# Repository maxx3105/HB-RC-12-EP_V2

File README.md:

# HB-RC-12-EP_V2
12 Tasten Fernbedienung mit E-Paper Display für Homematic

Zusätzlich die Option das E-Paper Display direkt anzuschließen und LiPo Akku per QI Ladefunktion aufzuladen.

Dieses Projekt basiert auf der Arbeit von [pa-pa](https://github.com/pa-pa/AskSinPP) ,[Jérôme](https://github.com/jp112sdl/HB-RC-4-Dis-TH) und [MajorTom](https://github.com/TomMajor/SmartHome/tree/master/PCB/HB-RC-12-EP).

# Hardware

### Bauteile

Bauteile                   | Bezeichnung          | Anzahl | Kommentar        | Quelle   |
-------------------------- | -------------------- | ------ | ---------------- | -------- |
C1,C2,C14,C15,C16,C17      | 100nF, 10%, 50V      |   6    |  X7R-G0805 100N  |Reichelt  |
C18                        | 100µF/10V            |   1    | TAJ 3528 100/10  |Reichelt  |
D1                         | LED rot 12 mcd 160°  |   1    | OSO LHR974       |Reichelt  |
D2                         | LED grün 7.1 mcd 160°|   1    | OSO LGR971       |Reichelt  |
R1, R2                     | 1,5K Ohm             |   2    | RND 0805 1 1,5K  |Reichelt  |
R3                         | 10K Ohm              |   1    | RND 0805 1 10K   |Reichelt  |
U1                         | Atmega 1284P-AU      |   1    | TQFP44           |Reichelt  |
U2                         | CC1101               |   1    | 868Mhz Funkmodul |[eBay](https://www.ebay.de/itm/1-2-5PCS-CC1101-868MHZ-Kabellos-Modul-Long-Distance-Transmission-Antenne-1-8V/322983173720?ssPageName=STRK%3AMEBIDX%3AIT&var=512121286081&_trksid=p2057872.m2749.l2649)|
SW1-13                     | Taster 3x6x2,5mm     |  13    | DTSM-3           |[Aliexpress](https://de.aliexpress.com/item/32672806661.html)|
Q1                         | CSTCE8               |   1    | 8Mhz Resonator   |[Aliexpress](https://de.aliexpress.com/item/32436805954.html?spm=a2g0s.9042311.0.0.27424c4dFOxBvK)|
Q3 Statt Q1                | CSTCC8               |   1    | 8Mhz Resonator   |Reichelt  |

Bauteile ohne Hat          | Bezeichnung          | Anzahl | Kommentar        | Quelle |
-------------------------- | -------------------- | ------ | ---------------- | ------ |
C3-C13                     | 1µF, 10%, 25V        |  11    | KEM X5R0805 1,0U |Reichelt|
D3, D4, D5                 | MBR0530              |   3    | MBR0530T1G ONS   |Reichelt|
C3, ... C13                | 1µF, 10%, 25V        |  11    | KEM X5R0805 1,0U |Reichelt|
R8                         | 100K Ohm             |   1    | RND 0805 1 100K  |Reichelt|
R8-1,R8-2                  | 1,0 Ohm              |   2    | SMD-0805 1,00    |Reichelt|
Q2                         | IRLML 6346           |   1    | IRLML 6346       |Reichelt|
L1                         | Induktivität 68 µH   |   1    | L-1616FPS 68µ    |Reichelt|

Bauteile LiPo              | Bezeichnung          | Anzahl | Kommentar       | Quelle |
-------------------------- | -------------------- | ------ | --------------- | ------ |
C19,C20                    | 10uF, +-20%, 10V     |   2    | KEM X5R0805 10U |Reichelt|
D6                         | LED weiß 520 mcd 120°|   1    | SLO SMD-W0805-0 |Reichelt|
R9                         | 4,7K Ohm             |   1    | RND 0805 1 4,7K |Reichelt|
R10                        | 680 Ohm              |   1    | RND 0805 1 680  |Reichelt|
R11                        | 1K Ohm               |   1    | RND 0805 1 1,0K |Reichelt|
R13                        | 100K Ohm             |   1    | RND 0805 1 100K |Reichelt|
U3                         | MCP 1700T-3002E      |   1    | MCP 1700T-3002E |Reichelt|
U4                         | MCP 73831T-2ACI      |   1    | MCP 73831T-2ACI |Reichelt|
U5                         | PC357                |   1    | PC 357NJ0000F   |Reichelt|

#### Sonstiges

~8,3 cm Draht als Antenne

### Programmieradapter
- 1x ISP (z.B. [diesen hier](https://www.diamex.de/dxshop/USB-ISP-Programmer-fuer-Atmel-AVR-Rev2))

# Software

### Fuses
Ext:  0xFF
High: 0xD2
Low:  0xE2 (0xFF für Externen Takt)

`C:\Program Files (x86)\Arduino\hardware\tools\avr\bin> .\avrdude -C ..\etc\avrdude.conf -p m1284p -P com7 -c stk500 -U lfuse:w:0xE2:m -U hfuse:w:0xD2:m -U efuse:w:0xFF:m`

### Firmware

Projektverzeichnis: [HB-RC-12-EP](https://github.com/jp112sdl/HB-RC-12-EP)

Benötigt werden die Bibliotheken
  - [AskSinPP](https://github.com/pa-pa/AskSinPP) (master-Branch verwenden!)
  - [Low-Power](https://github.com/rocketscream/Low-Power)
  - [EnableInterrupt](https://github.com/GreyGnome/EnableInterrupt)
  - [GxEPD](https://github.com/ZinggJM/GxEPD) 
  - [Adafruit-GFX](https://github.com/adafruit/Adafruit-GFX-Library)
  - [Adafruit-BusIO](https://github.com/adafruit/Adafruit_BusIO)
  - [U8g2_for_Adafruit_GFX](https://github.com/olikraus/U8g2_for_Adafruit_GFX)

# Bauanleitung

https://cdn.thingiverse.com/assets/88/70/7e/3d/6d/Aufbauanleitung_YA_HB-RC-12-EP_Case.pdf

# Bilder

# Links
https://homematic-forum.de/forum/viewtopic.php?f=76&t=50160

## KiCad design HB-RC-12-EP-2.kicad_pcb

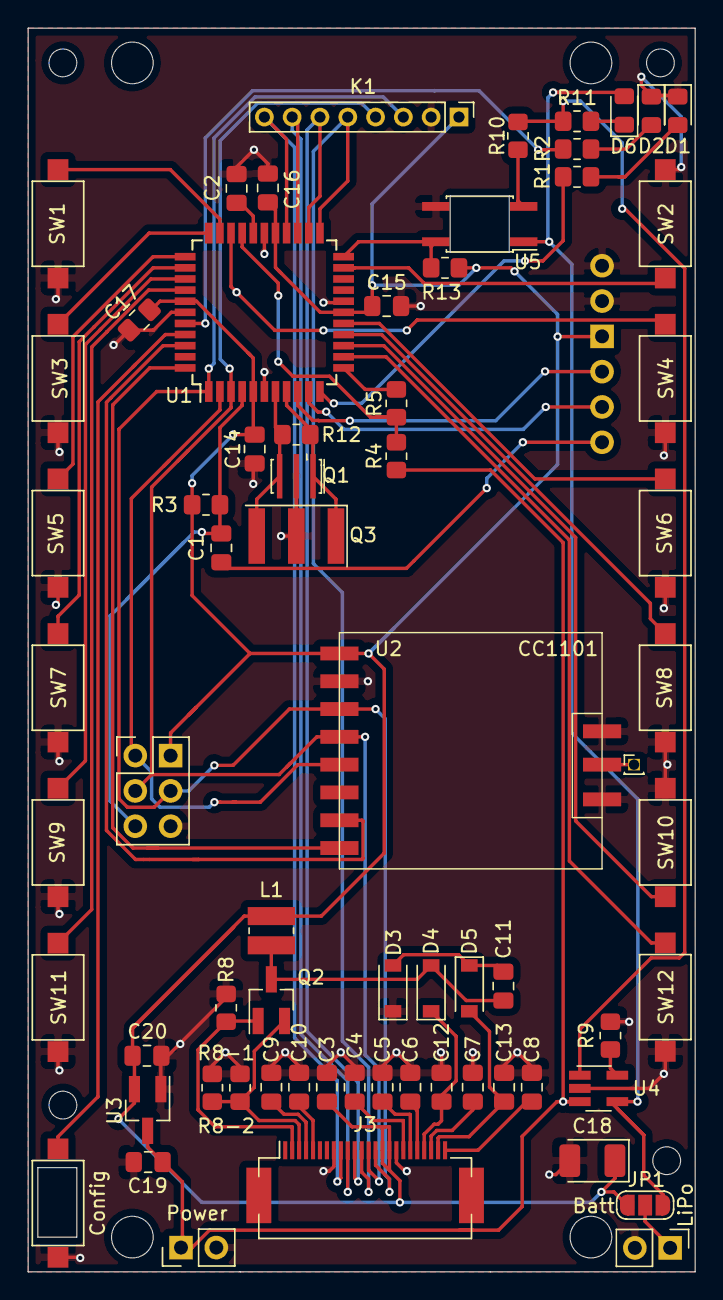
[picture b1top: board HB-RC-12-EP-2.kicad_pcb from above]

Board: 2 copper layers, 48.0 x 89.5 mm, 69 parts (1 on the bottom side), 59 nets.

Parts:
+: Power; PinHeader_1x02_P2.54mm_Vertical
Ant: Ant; PinHeader_1x01_P1.00mm_Vertical
C1, C2, C14, C15, C16, C17: 100n; C_0805_2012Metric_Pad1.18x1.45mm_HandSolder
C3, C4, C5, C6, C7, C8: 1µF/25V; C_0805_2012Metric_Pad1.18x1.45mm_HandSolder
C9, C10, C11, C12, C13: 1µF/50V; C_0805_2012Metric_Pad1.18x1.45mm_HandSolder
C18: 100µ/10V; CP_EIA-3528-21_Kemet-B_Pad1.50x2.35mm_HandSolder
C19, C20: 10/10; C_0805_2012Metric_Pad1.18x1.45mm_HandSolder
Config: SW_Push; SW_SPST_CK_RS282G05A3
D1: LED rt; LED_0805_2012Metric_Pad1.15x1.40mm_HandSolder
D2: gn; LED_0805_2012Metric_Pad1.15x1.40mm_HandSolder
D3, D4, D5: MBR0530; D_SOD-123
D6: LED wt; LED_0805_2012Metric_Pad1.15x1.40mm_HandSolder
FTDI1: FTDI; PinHeader_1x06_P2.54mm_Vertical
ISP1: ISP; PinHeader_2x03_P2.54mm_Vertical
J3: eInk; Hirose_FH12-24S-0.5SH_1x24-1MP_P0.50mm_Horizontal
JP1: SolderJumper_3_Open; SolderJumper-3_P1.3mm_Open_RoundedPad1.0x1.5mm_NumberLabels
K1: ePaper; PinHeader_1x08_P2.00mm_Vertical
L1: 68µH; L_Wuerth_MAPI-3012
Power: Batt; PinHeader_1x02_P2.54mm_Vertical
Q1: CSTCE8; Resonator_SMD_muRata_CSTxExxV-3Pin_3.0x1.1mm_HandSoldering
Q2: IRLML6346TRBPF; SOT-23_Handsoldering
Q3: CSTCC8; Resonator_SMD_muRata_SFECV-3Pin_6.9x2.9mm
R1, R2: 1,5k; R_0805_2012Metric_Pad1.20x1.40mm_HandSolder
R3: 10k; R_0805_2012Metric_Pad1.20x1.40mm_HandSolder
R4: 470k; R_0805_2012Metric_Pad1.20x1.40mm_HandSolder
R5, R8, R13: 100k; R_0805_2012Metric_Pad1.20x1.40mm_HandSolder
R8-1, R8-2: 1; R_0805_2012Metric_Pad1.20x1.40mm_HandSolder
R9: 4k7; R_0805_2012Metric_Pad1.20x1.40mm_HandSolder
R10: 680; R_0805_2012Metric_Pad1.20x1.40mm_HandSolder
R11: 1k; R_0805_2012Metric_Pad1.20x1.40mm_HandSolder
R12: 1M; R_0805_2012Metric_Pad1.20x1.40mm_HandSolder
SW1, SW2, SW3, SW4, SW5, SW6, SW7, SW8, SW9, SW10, SW11, SW12: SW_Push; SW_SPST_CK_RS282G05A3
U1: ATmega1284P-AU; TQFP-44_10x10mm_P0.8mm
U2: CC1101; CC1101_SMD
U3: MCP 1700T-3002E; SOT-23_Handsoldering
U4: MCP73831T-2ACI/OT; SOT-23-5_HandSoldering
U5: PC357; SO-4_4.4x3.6mm_P2.54mm

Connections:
+3V0: C3.1, C14.1, C15.1, C16.1, C17.1, C18.1, C20.1, FTDI1.3, ISP1.2, J3.15, J3.16, JP1.1, K1.1, L1.1, R3.1, R13.1, U1.5, U1.17, U1.27, U1.38, U2.1, U3.2
+BATT: C19.1, Power.1, R4.1, U3.3, U4.3
/A0: SW11.2, U1.37
/A1: SW9.2, U1.36
/A2: SW7.2, U1.35
/A3: SW5.2, U1.34
/A4: SW3.2, U1.33
/A5: SW1.2, U1.32
/A6: SW4.2, U1.31
/A7: R4.2, R5.1, U1.30
/B_CHARGING: R13.2, U1.22, U5.4
/C2: SW2.2, U1.21
/CC1101_CS: U1.44, U2.8
/CC1101_GDO0: U1.42, U2.7
/CONF: Config.2, U1.41
/D3: R5.2, U1.12
/D4: SW12.2, U1.13
/D5: SW10.2, U1.14
/D6: SW8.2, U1.15
/D7: SW6.2, U1.16
/DTR: C1.2, FTDI1.6
/GDR: J3.2, Q2.1, R8.1
/GX_BSY: J3.9, K1.8, U1.26
/GX_CS: J3.12, K1.5, U1.23
/GX_DC: J3.11, K1.6, U1.24
/GX_RST: J3.10, K1.7, U1.25
/LED: R1.1, U1.11
/LED2: R2.1, U1.40
/MISO: ISP1.1, U1.2, U2.5
/MOSI: ISP1.4, J3.14, K1.3, U1.1, U2.3
/PREVGH: C12.1, D4.1, J3.21
/PREVGL: C13.2, D5.2, J3.23
/RESE: J3.3, Q2.2, R8-1.1, R8-2.1
/RESET: C1.1, ISP1.5, R3.2, U1.4
/RXD: FTDI1.4, U1.9
/SCK: ISP1.3, J3.13, K1.4, U1.3, U2.4
/TXD: FTDI1.5, U1.10
GND: +.2, C2.2, C3.2, C4.2, C5.2, C6.2, C7.2, C8.2, C9.2, C10.2, C12.2, C13.1, C14.2, C15.2, C16.2, C17.2, C18.2, C19.2, C20.2, Config.1, D1.1, D2.1, D3.1, FTDI1.1, FTDI1.2, ISP1.6, J3.8, J3.17, K1.2, Power.2, Q1.2, Q3.2, R8.2, R8-1.2, R8-2.2, R9.2, SW1.1, SW2.1, SW3.1, SW4.1, SW5.1, SW6.1, SW7.1, SW8.1, SW9.1, SW10.1, SW11.1, SW12.1, U1.6, U1.18, U1.28, U1.39, U2.2, U2.10, U2.11, U3.1, U4.2, U5.3
unnamed: C2.1, U1.29
unnamed: C4.1, J3.18
unnamed: C5.1, J3.19
unnamed: C6.1, J3.20
unnamed: C7.1, J3.22
unnamed: C8.1, J3.24
unnamed: C9.1, J3.4
unnamed: C10.1, J3.5
unnamed: C11.1, D4.2, L1.2, Q2.3
unnamed: C11.2, D3.2, D5.1
unnamed: D1.2, R1.2
unnamed: D2.2, R2.2
unnamed: D6.1, R11.2
unnamed: D6.2, JP1.3, U4.4, U5.1
unnamed: Ant.1, U2.9
unnamed: +.1, JP1.2
unnamed: Q1.1, Q3.1, R12.1, U1.8
unnamed: Q1.3, Q3.3, R12.2, U1.7
unnamed: R9.1, U4.5
unnamed: R10.1, R11.1, U4.1
unnamed: R10.2, U5.2

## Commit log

2021-03-10 Add files via upload
    Bugfix
2021-03-13 Add files via upload
    Change some footprints to handsolder. Add CSTCE.
2021-03-13 Update README.md
    Add CSTCC8 Resonator.
2021-03-27 Bugfix
2022-01-30 Add PC357
